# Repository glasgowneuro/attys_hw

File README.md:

# Attys Hardware design

The PCB has been designed with EAGLE.

Copyright 2016 Glasgow Neuro LTD & Bernd Porr

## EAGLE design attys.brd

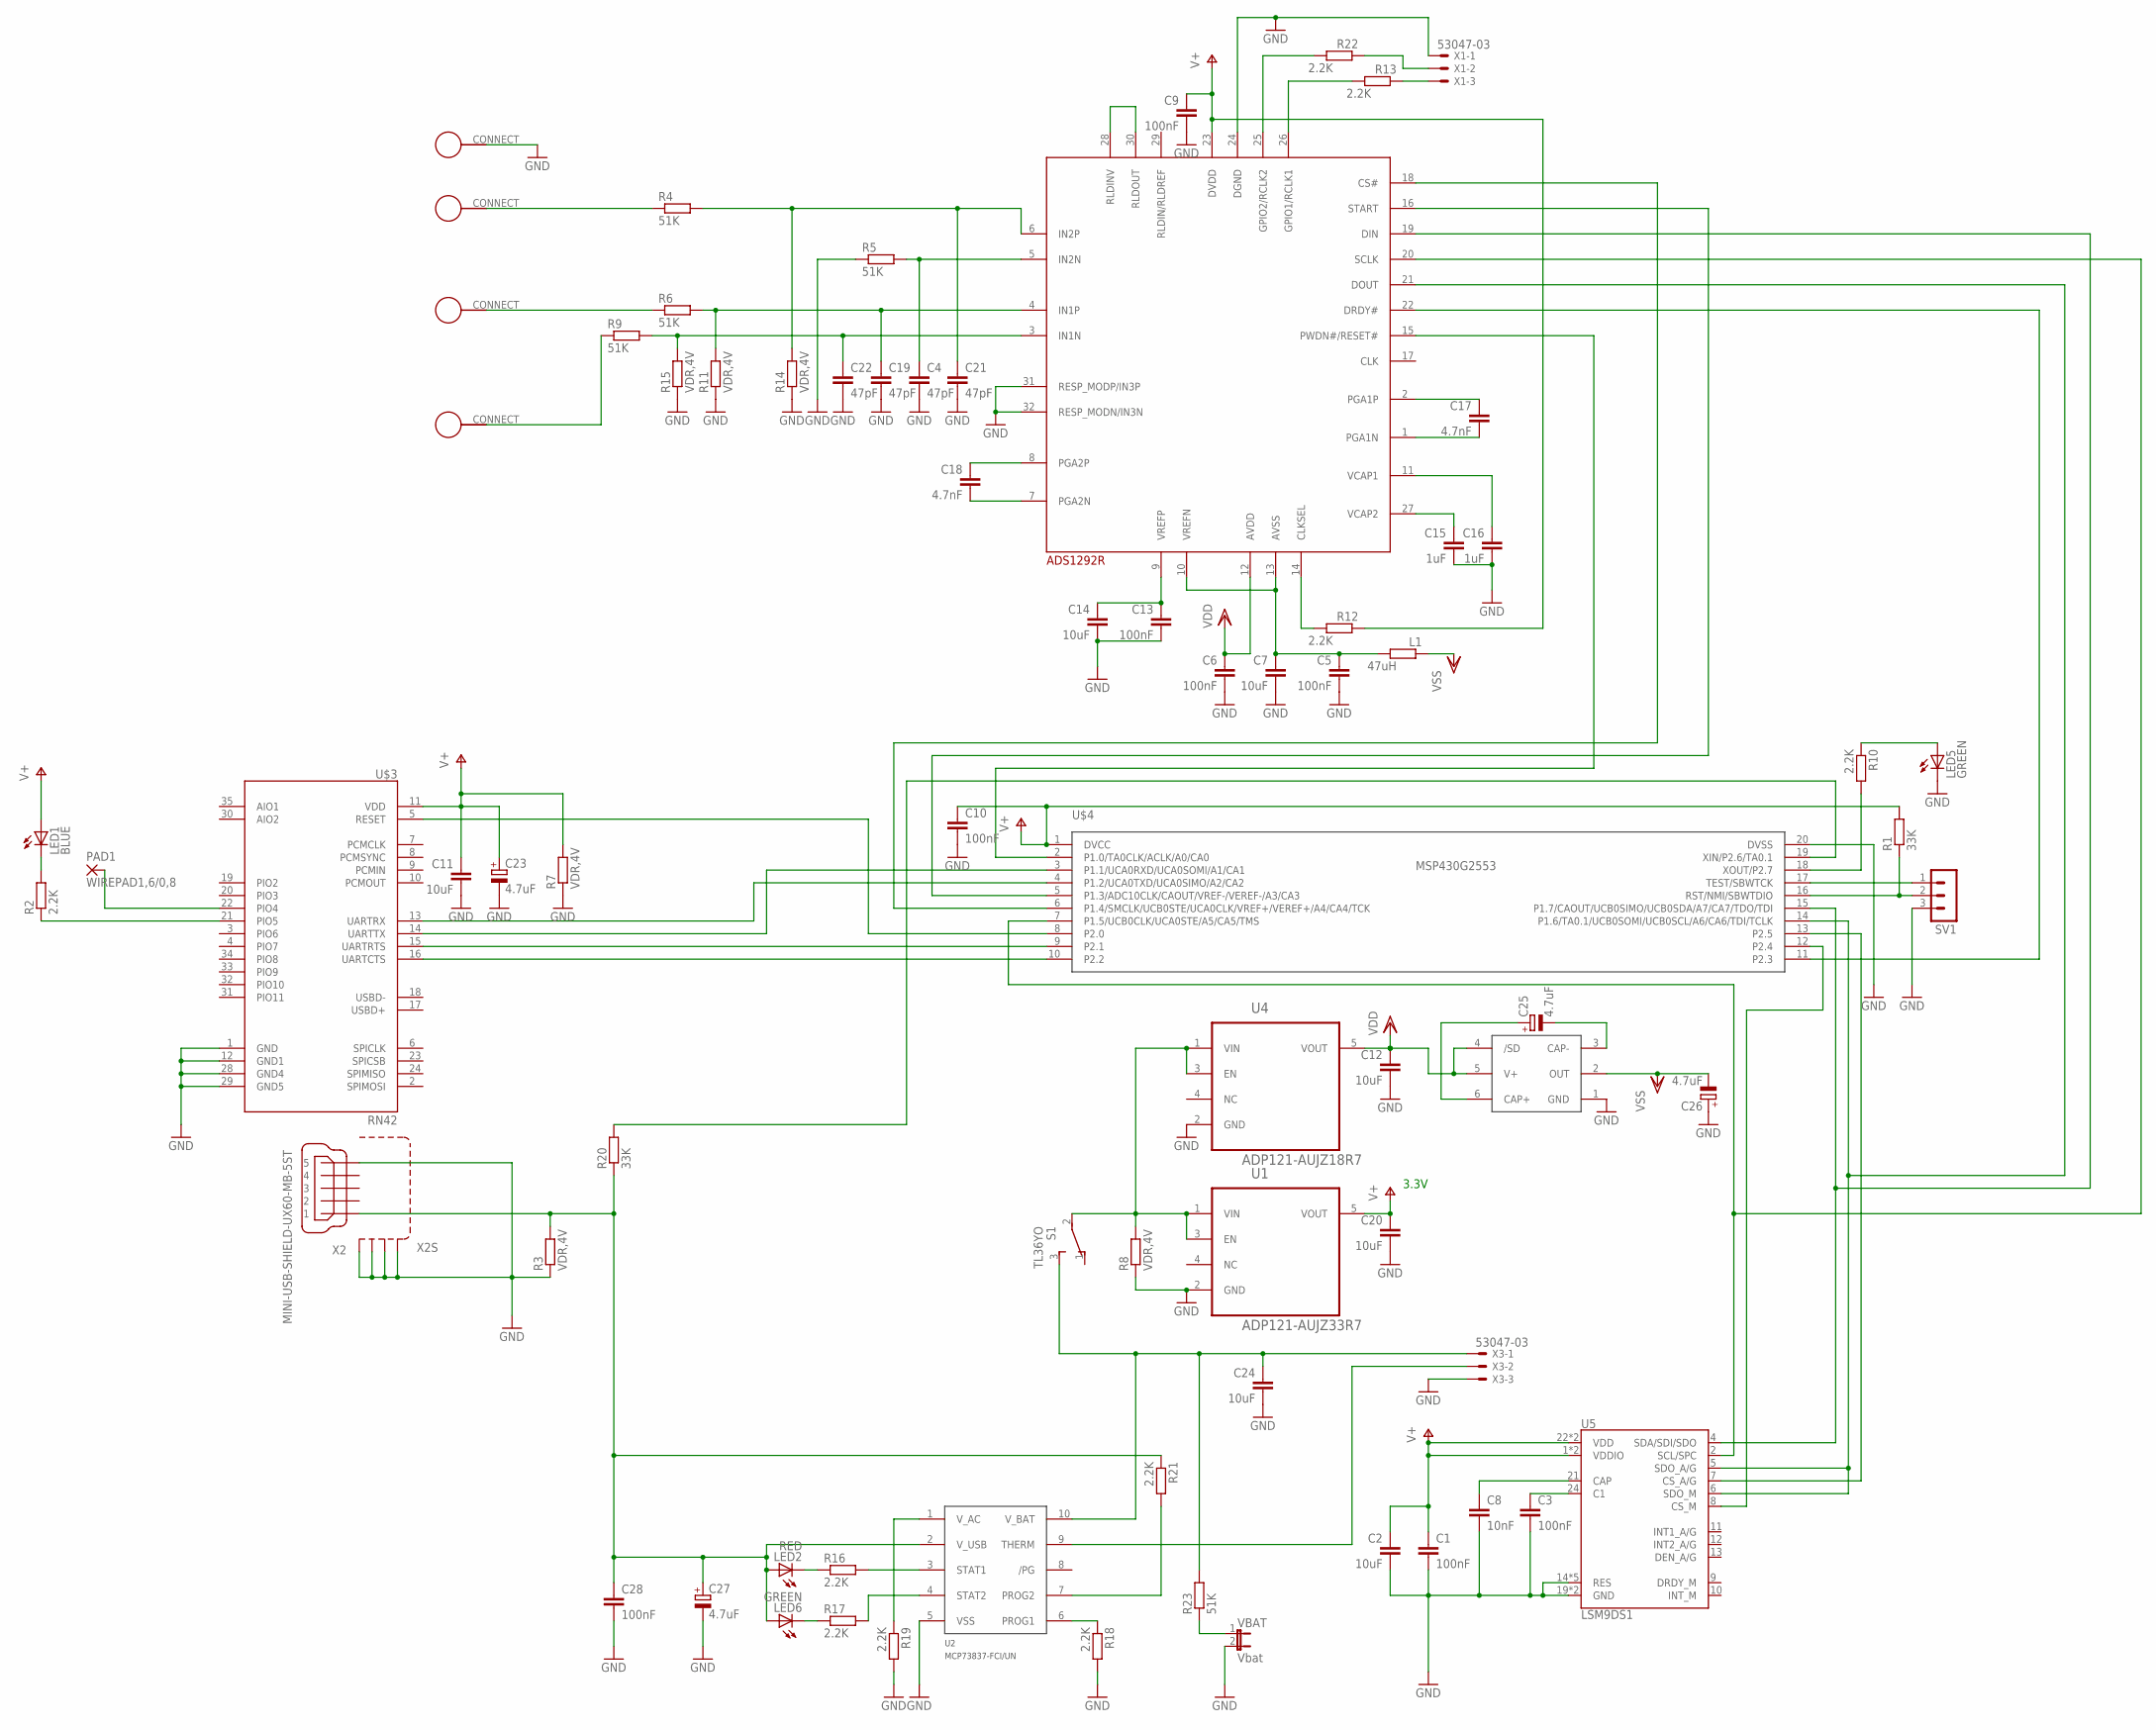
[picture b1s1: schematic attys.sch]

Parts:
ADS1292R: ADS1292R; TQFP-32
C1, C3, C5, C6, C9, C10, C13, C28: 100nF; C0603
C2, C7, C11, C12, C14, C20, C24: 10uF; C1206
C4, C19, C21, C22: 47pF; C0603
C8: 10nF; C0603
C15, C16: 1uF; C0603
C17, C18: 4.7nF; C0603
C23, C25, C26, C27: 4.7uF; SMC_C
L1: 47uH; R0805
LED1: BLUE; CHIPLED_0805
LED2: RED; CHIPLED_0805
LED5, LED6: GREEN; CHIPLED_0805
PAD1: WIREPAD1,6/0,8; 1,6/0,8
R1, R20: 33K; R0603
R2, R10, R12, R13, R16, R17, R18, R19, R21, R22: 2.2K; R0603
R3, R7, R8, R11, R14, R15: VDR,4V; R0805
R4, R5, R6, R9, R23: 51K; R0603
S1: TL36YO; TL3XYO
SV1: MA03-1
U1: ADP121-AUJZ33R7; SOT95P280X100-5N
U2: MCP73837-FCI/UN; MSOP10
U4: ADP121-AUJZ18R7; SOT95P280X100-5N
U5: LSM9DS1; LGA24-8X4
U$3: RN42; SPARKFUN_RN41
U$4: MSP430G2553; TSSOP20
U$5, U$7, U$9, U$10: 4MMCONNECT
U$12: LM2664; SOT-23-5
VBAT: Vbat; JP1
X1, X3: 53047-03
X2: MINI-USB-SHIELD-UX60-MB-5ST; UX60-MB-5ST

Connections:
+5V: C27.+, C28.1, LED2.A, LED6.A, R3.2, R20.1, R21.1, U2.2 (V_USB), X2.1
CS/: U5.8 (CS_M), U$4.12 (P2.4)
ECG_/CS: ADS1292R.18 (CS#), U$4.6 (P1.4/SMCLK/UCB0STE/UCA0CLK/VREF+/VEREF+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)
ECG_/DRDY: ADS1292R.22 (DRDY#), U$4.11 (P2.3)
ECG_START: ADS1292R.16 (START), U$4.5 (P1.3/ADC10CLK/CAOUT/VREF-/VEREF-/A3/CA3)
GND: ADS1292R.24 (DGND), ADS1292R.31 (RESP_MODP/IN3P), ADS1292R.32 (RESP_MODN/IN3N), C1.2, C2.2, C3.2, C4.2, C5.2, C6.2, C7.2, C8.2, C9.2, C10.2, C11.2, C12.2, C13.2, C14.2, C15.2, C16.2, C19.2, C20.2, C21.2, C22.2, C23.-, C24.2, C26.+, C27.-, C28.2, LED5.C, R3.1, R5.1, R7.1, R8.1, R11.1, R14.1, R15.1, R18.2, R19.2, SV1.3, U1.2 (GND), U2.5 (VSS), U4.2 (GND), U5.14 (RES), U5.15 (RES), U5.16 (RES), U5.17 (RES), U5.18 (RES), U5.19 (GND), U5.20 (GND), U$3.1 (GND), U$3.12 (GND1), U$3.28 (GND4), U$3.29 (GND5), U$4.20 (DVSS), U$5.CONNECT, U$12.1 (GND), VBAT.2, X1.1, X2.5, X2.M1 (S1), X2.M2 (S2), X2.M3 (S3), X2.M4 (S4), X3.3
unnamed: R1.1, SV1.2, U$4.16 (RST/NMI/SBWTDIO)
unnamed: U$3.13 (UARTRX), U$4.4 (P1.2/UCA0TXD/UCA0SIMO/A2/CA2)
unnamed: ADS1292R.28 (RLDINV), ADS1292R.30 (RLDOUT)
unnamed: ADS1292R.5 (IN2N), C4.1, R5.2
unnamed: SV1.1, U$4.17 (TEST/SBWTCK)
unnamed: U$3.14 (UARTTX), U$4.3 (P1.1/UCA0RXD/UCA0SOMI/A1/CA1)
unnamed: U$3.15 (UARTRTS), U$4.9 (P2.1)
unnamed: U$3.16 (UARTCTS), U$4.10 (P2.2)
unnamed: U$3.5 (RESET), U$4.8 (P2.0)
unnamed: R2.1, U$3.21 (PIO5)
unnamed: R8.2, S1.2, U1.1 (VIN), U1.3 (EN), U4.1 (VIN), U4.3 (EN)
unnamed: ADS1292R.10 (VREFN), ADS1292R.13 (AVSS), C5.1, C7.1, L1.2
unnamed: PAD1.1, U$3.22 (PIO4)
unnamed: R10.2, U$4.18 (XOUT/P2.7)
unnamed: LED5.A, R10.1
unnamed: LED1.C, R2.2
unnamed: ADS1292R.25 (GPIO2/RCLK2), R22.2
unnamed: ADS1292R.9 (VREFP), C13.1, C14.1
unnamed: ADS1292R.27 (VCAP2), C15.1
unnamed: ADS1292R.26 (GPIO1/RCLK1), R13.2
unnamed: ADS1292R.11 (VCAP1), C16.1
unnamed: R20.2, U$4.19 (XIN/P2.6/TA0.1)
unnamed: ADS1292R.15 (PWDN#/RESET#), U$4.2 (P1.0/TA0CLK/ACLK/A0/CA0)
unnamed: U5.7 (CS_A/G), U$4.13 (P2.5)
unnamed: C3.1, U5.24 (C1)
unnamed: C8.1, U5.21 (CAP)
unnamed: R13.1, X1.3
unnamed: R22.1, X1.2
unnamed: R23.1, VBAT.1
unnamed: ADS1292R.2 (PGA1P), C17.1
unnamed: ADS1292R.1 (PGA1N), C17.2
unnamed: ADS1292R.8 (PGA2P), C18.1
unnamed: ADS1292R.7 (PGA2N), C18.2
unnamed: ADS1292R.14 (CLKSEL), R12.2
unnamed: ADS1292R.6 (IN2P), C21.1, R4.2, R14.2
unnamed: ADS1292R.3 (IN1N), C22.1, R9.2, R15.2
unnamed: ADS1292R.4 (IN1P), C19.1, R6.2, R11.2
unnamed: R4.1, U$7.CONNECT
unnamed: R9.1, U$10.CONNECT
unnamed: R6.1, U$9.CONNECT
unnamed: C24.1, R23.2, S1.3 (S), U2.10 (V_BAT), X3.1
unnamed: C25.+, U$12.6 (CAP+)
unnamed: C25.-, U$12.3 (CAP-)
unnamed: R16.2, U2.3 (STAT1)
unnamed: LED6.C, R17.1
unnamed: R17.2, U2.4 (STAT2)
unnamed: LED2.C, R16.1
unnamed: R18.1, U2.6 (PROG1)
unnamed: U2.9 (THERM), X3.2
unnamed: R19.1, U2.1 (V_AC)
unnamed: R21.2, U2.7 (PROG2)
SPI_CLK: ADS1292R.20 (SCLK), U5.2 (SCL/SPC), U$4.7 (P1.5/UCB0CLK/UCA0STE/A5/CA5/TMS)
SPI_MISO: ADS1292R.21 (DOUT), U5.5 (SDO_A/G), U5.6 (SDO_M), U$4.14 (P1.6/TA0.1/UCB0SOMI/UCB0SCL/A6/CA6/TDI/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)
SPI_MOSI: ADS1292R.19 (DIN), U5.4 (SDA/SDI/SDO), U$4.15 (P1.7/CAOUT/UCB0SIMO/UCB0SDA/A7/CA7/TDO/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)
V+: ADS1292R.23 (DVDD), C1.1, C2.1, C9.1, C10.1, C11.1, C20.1, C23.+, LED1.A, R1.2, R7.2, R12.1, U1.5 (VOUT), U5.1 (VDDIO), U5.3 (VDDIO), U5.22 (VDD), U5.23 (VDD), U$3.11 (VDD), U$4.1 (DVCC)
VDD: ADS1292R.12 (AVDD), C6.1, C12.1, U4.5 (VOUT), U$12.4 (/SD), U$12.5 (V+)
VSS: C26.-, L1.1, U$12.2 (OUT)

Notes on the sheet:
3.3V

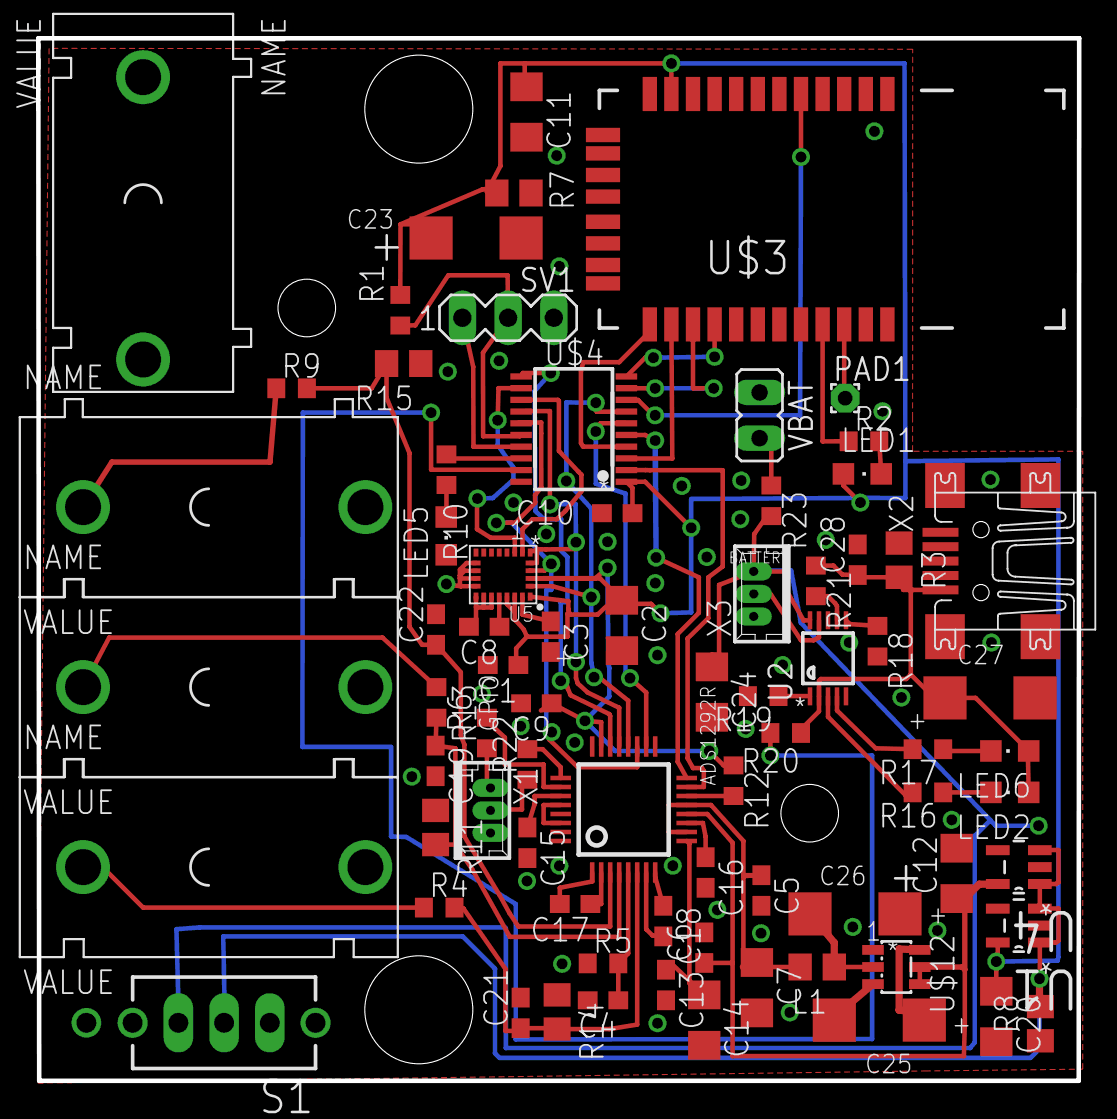
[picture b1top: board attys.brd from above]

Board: 2 copper layers, 57.8 x 57.9 mm, 75 parts (0 on the bottom side), 63 nets.

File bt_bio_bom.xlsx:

Attys, v0.98b
Qty | Value | Device | Package | Parts | Description | Farnell | RS
1 |  | MA03-1 | MA03-1 | SV1 | PIN HEADER | 3417657
8 | 100nF | C-EUC0603 | C0603 | C1, C3, C5, C6, C9, C10, C13, C28 | CAPACITOR, European symbol | 1759122
1 | 10nF | C-EUC0603 | C0603 | C8 | CAPACITOR, European symbol | 1759102
7 | 10uF | C-EUC1206 | C1206 | C2, C7, C11, C12, C14, C20, C24 | CAPACITOR, European symbol | 1458919
3 | 1uF | C-EUC0603 | C0603 | C15, C16, C29 | CAPACITOR, European symbol | 1759408
10 | 2.2K | R-EU_R0603 | R0603 | R2, R10, R12, R13, R16, R17, R18, R19, R21, R22 | RESISTOR, European symbol | 1469765
2 | 33K | R-EU_R0603 | R0603 | R1, R20 | RESISTOR, European symbol | 1469801
2 | 4.7nF | C-EUC0603 | C0603 | C17, C18 | CAPACITOR, European symbol | 2320809
4 | 4.7uF | CPOL-EUSMCC | SMC_C | C23, C25, C26, C27 | POLARIZED CAPACITOR, European symbol | 1754202
4 | 47pF | C-EUC0603 | C0603 | C4, C19, C21, C22 | CAPACITOR, European symbol | 1759062
1 | 47uH | R-EU_R0805 | R0805 | L1 | RESISTOR, European symbol | 2215655
4 | 4MMCONNECT | 4MMCONNECT | 4MMCONNECT | U$5, U$7, U$9, U$10 |  | 1101130
4 | 51K | R-EU_R0603 | R0603 | R4, R5, R6, R9 | RESISTOR, European symbol | 2447393
2 | 53047-03 | 53047-03 | 53047-03 | X1, X3 | CONNECTOR | 1022276
1 | ADP121-AUJZ18R7 | ADP121-AUJZ18R7 | SOT95P280X100-5N | U4 | 150 mA, Low Quiescent Current, CMOS Linear Regulator | 4026763
1 | ADP121-AUJZ33R7 | ADP121-AUJZ33R7 | SOT95P280X100-5N | U1 | 150 mA, Low Quiescent Current, CMOS Linear Regulator | 4026766
1 | ADS1292RIPBS | ADS1292RIPBS | TQFP-32 | ADS1292R | Analogue Front End IC, 2-Channel 24 bit, 8ksps SPI |  | 162-6118
1 | BLUE | LEDCHIPLED_0805 | CHIPLED_0805 | LED1 | LED | 1716765
2 | GREEN | LEDCHIPLED_0805 | CHIPLED_0805 | LED5, LED6 | LED | 2112116
1 | LM2664 | LM2664 | SOT-23-5 | U$12 |  | 3123021
1 | LSM9DS1 | LSM9DS1 | LGA24-8X4 | U5 | LSM9DS1 3D accelerometer, gyroscope & magnetometer | 2532383
1 | MCP73837-FCI/UN | MCP73837 | MSOP10 | U2 |  | 1675426
1 | MINI-USB-SHIELD-UX60-MB-5ST | MINI-USB-SHIELD-UX60-MB-5ST | UX60-MB-5ST | X2 | MINI USB Connector | 2293774
1 | MSP430G2553IPW20R | MSP430G2553IPW20R | TSSOP20 | U$4 |  | 3123284
1 | RED | LEDCHIPLED_0805 | CHIPLED_0805 | LED2 | LED | 2099241
1 | RN4678 | RN4678 | RN4678 | U$1 |  | 3580729
1 | TL36YO | TL36YO | TL3XYO | S1 | TINY SWITCH ON - ON | 1550095
6 | VDR,4V | R-EU_R0805 | R0805 | R3, R7, R8, R11, R14, R15 | RESISTOR, European symbol | 8832463
1 | Vbat | JP1E | JP1 | VBAT | JUMPER | CN09983

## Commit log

2023-08-15 Current version being sold
2023-08-15 switched to RN4678
2023-08-15 Small fixes in the layout
2023-08-19 Tested with actual bluetooth module and it seems to work.
2023-08-19 Added more GND vias
2023-08-21 Version European Circiuts
2023-08-22 Fixed BOM with feedback from European circuits
2024-03-05 Updated LED oder code
2025-09-10 Renamed to be consistent
2025-09-10 Added license
2025-09-11 Created proper readme.
